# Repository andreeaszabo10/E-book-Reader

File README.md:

Szabo Cristina-Andreea
# E-book Reader
The project (Openbook) is an E-book reader built around the ESP32-C6-WROOM-1-N8 microcontroller, which integrates Wi-Fi and Bluetooth Low Energy functionality. It is responsible for managing communication between the connected components, sensor data acquisition, and display handling. The E-book reader has a 7.5-inch e-paper display, USB-C charging, a Li-Po battery, and 3 buttons.

## Block diagram:

## BOM - Bill of materials
| Component       | Device                | Link                                                                 | Datasheet                                                                 |
|-----------------|-----------------------|----------------------------------------------------------------------|---------------------------------------------------------------------------|
| BOOT_BUTTON     | BUTTON_CUSYOMV1        | [Link](https://ro.mouser.com/ProductDetail/Panasonic/EVQ-P7L01P?qs=rJ%252BziJWpyszWhhNszc02jQ%3D%3D&_gl=1*xzqk3l*_ga*dW5kZWZpbmVk*_ga_15W4STQT4T*dW5kZWZpbmVk*_ga_1KQLCYKRX3*dW5kZWZpbmVk)     | [Datasheet](https://componentsearchengine.com/Datasheets/2/EVQP7L01P.pdf) |
| C1              | ESP32_WROVER_EAGLE-LTSPICE_CC0402 | [Link](https://ro.mouser.com/ProductDetail/YAGEO/CC0402MRX5R5BB106?qs=zEY9bCHj09eCmUJdZuS5Lg%3D%3D)  | [Datasheet](https://componentsearchengine.com/Datasheets/2/CC0402MRX5R5BB106.pdf) |
| C1_BAT          | ESP32_WROVER_EAGLE-LTSPICE_CC0402 | [Link](https://ro.mouser.com/ProductDetail/YAGEO/CC0402MRX5R5BB106?qs=zEY9bCHj09eCmUJdZuS5Lg%3D%3D)  | [Datasheet](https://componentsearchengine.com/Datasheets/2/CC0402MRX5R5BB106.pdf) |
| C1_BAT1         | EAGLE-LTSPICE_CC0402   | [Link](https://ro.mouser.com/ProductDetail/YAGEO/CC0402MRX5R5BB106?qs=zEY9bCHj09eCmUJdZuS5Lg%3D%3D)  | [Datasheet](https://componentsearchengine.com/Datasheets/2/CC0402MRX5R5BB106.pdf) |
| C1_BAT2         | EAGLE-LTSPICE_CC0402   | [Link](https://ro.mouser.com/ProductDetail/YAGEO/CC0402MRX5R5BB106?qs=zEY9bCHj09eCmUJdZuS5Lg%3D%3D)  | [Datasheet](https://componentsearchengine.com/Datasheets/2/CC0402MRX5R5BB106.pdf) |
| C2              | ESP32_WROVER_EAGLE-LTSPICE_CC0402 | [Link](https://ro.mouser.com/ProductDetail/YAGEO/CC0402MRX5R5BB106?qs=zEY9bCHj09eCmUJdZuS5Lg%3D%3D)  | [Datasheet](https://componentsearchengine.com/Datasheets/2/CC0402MRX5R5BB106.pdf) |
| C2_BAT          | ESP32_WROVER_EAGLE-LTSPICE_CC0402 | [Link](https://ro.mouser.com/ProductDetail/YAGEO/CC0402MRX5R5BB106?qs=zEY9bCHj09eCmUJdZuS5Lg%3D%3D)  | [Datasheet](https://componentsearchengine.com/Datasheets/2/CC0402MRX5R5BB106.pdf) |
| C3              | RCL_CPOL-EUCT3528      | [Link](https://ro.mouser.com/ProductDetail/YAGEO/CC0402MRX5R5BB106?qs=zEY9bCHj09eCmUJdZuS5Lg%3D%3D)  | [Datasheet](https://componentsearchengine.com/Datasheets/2/CC0402MRX5R5BB106.pdf) |
| C4              | ESP32_WROVER_EAGLE-LTSPICE_CC0402 | [Link](https://ro.mouser.com/ProductDetail/YAGEO/CC0402MRX5R5BB106?qs=zEY9bCHj09eCmUJdZuS5Lg%3D%3D)  | [Datasheet](https://componentsearchengine.com/Datasheets/2/CC0402MRX5R5BB106.pdf) |
| C4_USB          | ESP32_WROVER_EAGLE-LTSPICE_CC0402 | [Link](https://ro.mouser.com/ProductDetail/YAGEO/CC0402MRX5R5BB106?qs=zEY9bCHj09eCmUJdZuS5Lg%3D%3D)  | [Datasheet](https://componentsearchengine.com/Datasheets/2/CC0402MRX5R5BB106.pdf) |
| C5              | ESP32_WROVER_EAGLE-LTSPICE_CC0402 | [Link](https://ro.mouser.com/ProductDetail/YAGEO/CC0402MRX5R5BB106?qs=zEY9bCHj09eCmUJdZuS5Lg%3D%3D)  | [Datasheet](https://componentsearchengine.com/Datasheets/2/CC0402MRX5R5BB106.pdf) |
| C5_USB          | ESP32_WROVER_EAGLE-LTSPICE_CC0402 | [Link](https://ro.mouser.com/ProductDetail/YAGEO/CC0402MRX5R5BB106?qs=zEY9bCHj09eCmUJdZuS5Lg%3D%3D)  | [Datasheet](https://componentsearchengine.com/Datasheets/2/CC0402MRX5R5BB106.pdf) |
| C6              | ESP32_WROVER_EAGLE-LTSPICE_CC0402 | [Link](https://ro.mouser.com/ProductDetail/YAGEO/CC0402MRX5R5BB106?qs=zEY9bCHj09eCmUJdZuS5Lg%3D%3D)  | [Datasheet](https://componentsearchengine.com/Datasheets/2/CC0402MRX5R5BB106.pdf) |
| C7              | ESP32_WROVER_EAGLE-LTSPICE_CC0402 | [Link](https://ro.mouser.com/ProductDetail/YAGEO/CC0402MRX5R5BB106?qs=zEY9bCHj09eCmUJdZuS5Lg%3D%3D)  | [Datasheet](https://componentsearchengine.com/Datasheets/2/CC0402MRX5R5BB106.pdf) |
| C8              | ESP32_WROVER_EAGLE-LTSPICE_CC0402 | [Link](https://ro.mouser.com/ProductDetail/YAGEO/CC0402MRX5R5BB106?qs=zEY9bCHj09eCmUJdZuS5Lg%3D%3D)  | [Datasheet](https://componentsearchengine.com/Datasheets/2/CC0402MRX5R5BB106.pdf) |
| C9              | EAGLE-LTSPICE_CC0402   | [Link](https://ro.mouser.com/ProductDetail/YAGEO/CC0402MRX5R5BB106?qs=zEY9bCHj09eCmUJdZuS5Lg%3D%3D)  | [Datasheet](https://componentsearchengine.com/Datasheets/2/CC0402MRX5R5BB106.pdf) |
| C10             | ESP32_WROVER_EAGLE-LTSPICE_CC0402 | [Link](https://ro.mouser.com/ProductDetail/YAGEO/CC0402MRX5R5BB106?qs=zEY9bCHj09eCmUJdZuS5Lg%3D%3D)  | [Datasheet](https://componentsearchengine.com/Datasheets/2/CC0402MRX5R5BB106.pdf) |
| C10_SUPERCAP    | CPH3225A               | [Link](https://ro.mouser.com/ProductDetail/Seiko-Semiconductors/CPH3225A?qs=3etwrb1wR%252BhUOph6lAO7eg%3D%3D) | [Datasheet](https://ro.mouser.com/datasheet/2/360/Seiko_Instruments_MicroBattery_E_20230330_2024Jan_-3561061.pdf) |
| CHANGE_BUTTON   | BUTTON_CUSYOMV1        | [Link](https://ro.mouser.com/ProductDetail/Panasonic/EVQ-P7L01P?qs=rJ%252BziJWpyszWhhNszc02jQ%3D%3D&_gl=1*xzqk3l*_ga*dW5kZWZpbmVk*_ga_15W4STQT4T*dW5kZWZpbmVk*_ga_1KQLCYKRX3*dW5kZWZpbmVk)     | [Datasheet](https://componentsearchengine.com/Datasheets/2/EVQP7L01P.pdf) |
| C_DELAY         | ESP32_WROVER_EAGLE-LTSPICE_CC0402 | [Link](https://ro.mouser.com/ProductDetail/YAGEO/CC0402MRX5R5BB106?qs=zEY9bCHj09eCmUJdZuS5Lg%3D%3D)  | [Datasheet](https://componentsearchengine.com/Datasheets/2/CC0402MRX5R5BB106.pdf) |
| D1              | USBLC6-2SC6Y           | [Link](https://ro.mouser.com/ProductDetail/STMicroelectronics/USBLC6-2SC6Y?qs=gNDSiZmRJS%2FOgDexvXkdow%3D%3D) | [Datasheet](https://ro.mouser.com/datasheet/2/389/usblc6_2sc6y-1852505.pdf) |
| D2              | ESP32_WROVER_AVX...SD0805S020S1R0_AVX_... | [Link](https://eu.mouser.com/ProductDetail/KYOCERA-AVX/SD0805S020S1R0?qs=jCA%252BPfw4LHbpkAoSnwrdjw%3D%3D) | [Datasheet](http://datasheets.avx.com/schottky.pdf) |
| D3              | MBR0530               | [Link](https://www.snapeda.com/parts/MBR0530/Onsemi/view-part/?ref=eda) | [Datasheet](https://www.snapeda.com/parts/MBR0530/Onsemi/view-part/?ref=eda) |
| D4              | MBR0530               | [Link](https://www.snapeda.com/parts/MBR0530/Onsemi/view-part/?ref=eda) | [Datasheet](https://www.snapeda.com/parts/MBR0530/Onsemi/view-part/?ref=eda) |
| D5              | MBR0530               | [Link](https://www.snapeda.com/parts/MBR0530/Onsemi/view-part/?ref=eda) | [Datasheet](https://www.snapeda.com/parts/MBR0530/Onsemi/view-part/?ref=eda) |
| D6              | PGB1010603MR          | [Link](https://www.snapeda.com/parts/PGB1010603MR/Littelfuse/view-part/?ref=eda) | [Datasheet](https://www.snapeda.com/parts/PGB1010603MR/Littelfuse/view-part/?ref=eda) |
| D7              | ESP32_WROVER_AVX---SD0805S020S1R0_AVX_... | [Link](https://eu.mouser.com/ProductDetail/KYOCERA-AVX/SD0805S020S1R0?qs=jCA%252BPfw4LHbpkAoSnwrdjw%3D%3D) | [Datasheet](http://datasheets.avx.com/schottky.pdf) |
| D8              | PGB1010603MR          | [Link](https://www.snapeda.com/parts/PGB1010603MR/Littelfuse/view-part/?ref=eda) | [Datasheet](https://www.snapeda.com/parts/PGB1010603MR/Littelfuse/view-part/?ref=eda) |
| D9              | PGB1010603MR          | [Link](https://www.snapeda.com/parts/PGB1010603MR/Littelfuse/view-part/?ref=eda) | [Datasheet](https://www.snapeda.com/parts/PGB1010603MR/Littelfuse/view-part/?ref=eda) |
| D10             | PGB1010603MR          | [Link](https://www.snapeda.com/parts/PGB1010603MR/Littelfuse/view-part/?ref=eda) | [Datasheet](https://www.snapeda.com/parts/PGB1010603MR/Littelfuse/view-part/?ref=eda) |
| D11             | PGB1010603MR          | [Link](https://www.snapeda.com/parts/PGB1010603MR/Littelfuse/view-part/?ref=eda) | [Datasheet](https://www.snapeda.com/parts/PGB1010603MR/Littelfuse/view-part/?ref=eda) |
| D12             | PGB1010603MR          | [Link](https://www.snapeda.com/parts/PGB1010603MR/Littelfuse/view-part/?ref=eda) | [Datasheet](https://www.snapeda.com/parts/PGB1010603MR/Littelfuse/view-part/?ref=eda) |
| EPD_C1          | ESP32_WROVER_EAGLE-LTSPICE_CC0402 | [Link](https://ro.mouser.com/ProductDetail/YAGEO/CC0402MRX5R5BB106?qs=zEY9bCHj09eCmUJdZuS5Lg%3D%3D)  | [Datasheet](https://componentsearchengine.com/Datasheets/2/CC0402MRX5R5BB106.pdf) |
| EPD_C2          | ESP32_WROVER_EAGLE-LTSPICE_CC0402 | [Link](https://ro.mouser.com/ProductDetail/YAGEO/CC0402MRX5R5BB106?qs=zEY9bCHj09eCmUJdZuS5Lg%3D%3D)  | [Datasheet](https://componentsearchengine.com/Datasheets/2/CC0402MRX5R5BB106.pdf) |
| EPD_C5          | ESP32_WROVER_EAGLE-LTSPICE_CC0402 | [Link](https://ro.mouser.com/ProductDetail/YAGEO/CC0402MRX5R5BB106?qs=zEY9bCHj09eCmUJdZuS5Lg%3D%3D)  | [Datasheet](https://componentsearchengine.com/Datasheets/2/CC0402MRX5R5BB106.pdf) |
| EPD_C6          | ESP32_WROVER_EAGLE-LTSPICE_CC0402 | [Link](https://ro.mouser.com/ProductDetail/YAGEO/CC0402MRX5R5BB106?qs=zEY9bCHj09eCmUJdZuS5Lg%3D%3D)  | [Datasheet](https://componentsearchengine.com/Datasheets/2/CC0402MRX5R5BB106.pdf) |
| EPD_C7          | ESP32_WROVER_EAGLE-LTSPICE_CC0402 | [Link](https://ro.mouser.com/ProductDetail/YAGEO/CC0402MRX5R5BB106?qs=zEY9bCHj09eCmUJdZuS5Lg%3D%3D)  | [Datasheet](https://componentsearchengine.com/Datasheets/2/CC0402MRX5R5BB106.pdf) |
| EPD_C8          | ESP32_WROVER_EAGLE-LTSPICE_CC0402 | [Link](https://ro.mouser.com/ProductDetail/YAGEO/CC0402MRX5R5BB106?qs=zEY9bCHj09eCmUJdZuS5Lg%3D%3D)  | [Datasheet](https://componentsearchengine.com/Datasheets/2/CC0402MRX5R5BB106.pdf) |
| EPD_C9          | ESP32_WROVER_EAGLE-LTSPICE_CC0402 | [Link](https://ro.mouser.com/ProductDetail/YAGEO/CC0402MRX5R5BB106?qs=zEY9bCHj09eCmUJdZuS5Lg%3D%3D)  | [Datasheet](https://componentsearchengine.com/Datasheets/2/CC0402MRX5R5BB106.pdf) |
| EPD_C10         | ESP32_WROVER_EAGLE-LTSPICE_CC0402 | [Link](https://ro.mouser.com/ProductDetail/YAGEO/CC0402MRX5R5BB106?qs=zEY9bCHj09eCmUJdZuS5Lg%3D%3D)  | [Datasheet](https://componentsearchengine.com/Datasheets/2/CC0402MRX5R5BB106.pdf) |
| EPD_C11         | ESP32_WROVER_EAGLE-LTSPICE_CC0402 | [Link](https://ro.mouser.com/ProductDetail/YAGEO/CC0402MRX5R5BB106?qs=zEY9bCHj09eCmUJdZuS5Lg%3D%3D)  | [Datasheet](https://componentsearchengine.com/Datasheets/2/CC0402MRX5R5BB106.pdf) |
| EPD_C12         | ESP32_WROVER_EAGLE-LTSPICE_CC0402 | [Link](https://ro.mouser.com/ProductDetail/YAGEO/CC0402MRX5R5BB106?qs=zEY9bCHj09eCmUJdZuS5Lg%3D%3D)  | [Datasheet](https://componentsearchengine.com/Datasheets/2/CC0402MRX5R5BB106.pdf) |
| IC1             | BD5229G-TR            | [Link](https://ro.mouser.com/ProductDetail/ROHM-Semiconductor/BD5229G-TR?qs=4kLU8WoGk0vvnhrrYwdszw%3D%3D) | [Datasheet](https://fscdn.rohm.com/en/products/databook/datasheet/ic/power/voltage_detector/bd52xxg-e.pdf) |
| IC4             | XC6220A331MR-G        | [Link](https://ro.mouser.com/ProductDetail/Torex-Semiconductor/XC6220A331MR-G?qs=AsjdqWjXhJ8ZSWznL1J0gg%3D%3D) | [Datasheet](https://ro.mouser.com/datasheet/2/760/xc6220-3371556.pdf) |
| J1              | FH34SRJ-24S-0.5SH_99_ | [Link](https://ro.mouser.com/ProductDetail/Hirose-Connector/FH34SRJ-24S-0.5SH99?qs=vcbW%252B4%252BSTIpKBl5ap9J8Fw%3D%3D) | [Datasheet](https://ro.mouser.com/datasheet/2/185/FH34SRJ_24S_0_5SH_99__CL0580_1255_6_99_2DDrawing_0-1615044.pdf) |
| J2              | USB4110-GF-A          | [Link](https://ro.mouser.com/ProductDetail/GCT/USB4110-GF-A?qs=KUoIvG%2F9IlYiZvIXQjyJeA%3D%3D) | [Datasheet](https://ro.mouser.com/datasheet/2/837/GCT_USB4110_Product_Drawing___20k_cycles-3455479.pdf) |
| J3              | QWIIC_CONNECTORJS-1MM | [Link](https://ro.mouser.com/ProductDetail/SparkFun/PRT-14417?qs=wd5RIQLrsJhgdz%2FpmZ%2F3GQ%3D%3D) | [Datasheet](https://ro.mouser.com/datasheet/2/813/Qwiic_Connector_Datasheet-1223982.pdf) |
| J4              | 112A-TAAR-R03_ATTEND  | [Link](https://store.comet.srl.ro/Catalogue/Product/43497/) | [Datasheet](https://store.comet.srl.ro/Catalogue/Product/43497/) |
| L1              | 744043680IND_4828-WE-TPC_WRE | [Link](https://ro.mouser.com/ProductDetail/Wurth-Elektronik/744043680?qs=PGXP4M47uW6VkZq%252BkzjrHA%3D%3D) | [Datasheet](https://eu.mouser.com/ProductDetail/Wurth-Elektronik/744043680?qs=PGXP4M47uW6VkZq%252BkzjrHA%3D%3D) |
| PFMF.050.1      | ESP32C6_VARISTORCN1812 | [Link](https://ro.mouser.com/ProductDetail/KEMET/VE1812K401R050?qs=OycAS1CGnlizCtaoDVbQTA%3D%3D) | [Datasheet](https://www.mouser.co.uk/ProductDetail/EPCOS-TDK/B72520T0350K062?qs=dEfas%2FXlABIszF52uu7vrg%3D%3D) |
| Q1              | DMG2305UX-7           | [Link](https://ro.mouser.com/ProductDetail/Diodes-Incorporated/DMG2305UX-7?qs=L1DZKBg7t5F%2FNBHrjfxC%252Bg%3D%3D) | [Datasheet](https://www.diodes.com/assets/Datasheets/DMG2305UX.pdf) |
| Q2              | ESP32_WROVER_SPARKFUN-DISCRETESEMI_MOSFET_... | [Link](https://ro.mouser.com/ProductDetail/Diodes-Incorporated/DMG2305UX-7?qs=L1DZKBg7t5F%2FNBHrjfxC%252Bg%3D%3D) | [Datasheet](https://www.diodes.com/assets/Datasheets/DMG2305UX.pdf) |
| Q3              | D8                    | [Link](https://ro.mouser.com/ProductDetail/Vishay-Semiconductors/SI1308EDL-T1-GE3?qs=bX1%252BNvsK%2FBramh9tgpOaEw%3D%3D) | [Datasheet](https://componentsearchengine.com/part-view/SI1308EDL-T1-GE3/Vishay) |
| R1              | ESP32_WROVER_EAGLE-LTSPICE_RR0402 | [Link](https://ro.mouser.com/ProductDetail/YAGEO/RC0402FR-07100KL?qs=mnq%2FyloZIXzTlUn7JAHSWg%3D%3D) | [Datasheet](https://ro.mouser.com/datasheet/2/447/YAGEO_PYu_RC_Group_51_RoHS_L_12-3313492.pdf) |
| R1_PINH         | ESP32_WROVER_EAGLE-LTSPICE_RR0402 | [Link](https://ro.mouser.com/ProductDetail/YAGEO/RC0402FR-07100KL?qs=mnq%2FyloZIXzTlUn7JAHSWg%3D%3D) | [Datasheet](https://ro.mouser.com/datasheet/2/447/YAGEO_PYu_RC_Group_51_RoHS_L_12-3313492.pdf) |
| R1_PINH1        | ESP32_WROVER_EAGLE-LTSPICE_RR0402 | [Link](https://ro.mouser.com/ProductDetail/YAGEO/RC0402FR-07100KL?qs=mnq%2FyloZIXzTlUn7JAHSWg%3D%3D) | [Datasheet](https://ro.mouser.com/datasheet/2/447/YAGEO_PYu_RC_Group_51_RoHS_L_12-3313492.pdf) |
| R1_BAT          | ESP32_WROVER_EAGLE-LTSPICE_RR0402 | [Link](https://ro.mouser.com/ProductDetail/YAGEO/RC0402FR-07100KL?qs=mnq%2FyloZIXzTlUn7JAHSWg%3D%3D) | [Datasheet](https://ro.mouser.com/datasheet/2/447/YAGEO_PYu_RC_Group_51_RoHS_L_12-3313492.pdf) |
| R1_PWRUSB       | ESP32_WROVER_EAGLE-LTSPICE_RR0402 | [Link](https://ro.mouser.com/ProductDetail/YAGEO/RC0402FR-07100KL?qs=mnq%2FyloZIXzTlUn7JAHSWg%3D%3D) | [Datasheet](https://ro.mouser.com/datasheet/2/447/YAGEO_PYu_RC_Group_51_RoHS_L_12-3313492.pdf) |
| R2              | ESP32_WROVER_EAGLE-LTSPICE_RR0402 | [Link](https://ro.mouser.com/ProductDetail/YAGEO/RC0402FR-07100KL?qs=mnq%2FyloZIXzTlUn7JAHSWg%3D%3D) | [Datasheet](https://ro.mouser.com/datasheet/2/447/YAGEO_PYu_RC_Group_51_RoHS_L_12-3313492.pdf) |
| R2_PINH         | ESP32_WROVER_EAGLE-LTSPICE_RR0402 | [Link](https://ro.mouser.com/ProductDetail/YAGEO/RC0402FR-07100KL?qs=mnq%2FyloZIXzTlUn7JAHSWg%3D%3D) | [Datasheet](https://ro.mouser.com/datasheet/2/447/YAGEO_PYu_RC_Group_51_RoHS_L_12-3313492.pdf) |
| R2_PINH1        | ESP32_WROVER_EAGLE-LTSPICE_RR0402 | [Link](https://ro.mouser.com/ProductDetail/YAGEO/RC0402FR-07100KL?qs=mnq%2FyloZIXzTlUn7JAHSWg%3D%3D) | [Datasheet](https://ro.mouser.com/datasheet/2/447/YAGEO_PYu_RC_Group_51_RoHS_L_12-3313492.pdf) |
| R2_USB          | ESP32_WROVER_EAGLE-LTSPICE_RR0402 | [Link](https://ro.mouser.com/ProductDetail/YAGEO/RC0402FR-07100KL?qs=mnq%2FyloZIXzTlUn7JAHSWg%3D%3D) | [Datasheet](https://ro.mouser.com/datasheet/2/447/YAGEO_PYu_RC_Group_51_RoHS_L_12-3313492.pdf) |
| R2_USB1         | ESP32_WROVER_EAGLE-LTSPICE_RR0402 | [Link](https://ro.mouser.com/ProductDetail/YAGEO/RC0402FR-07100KL?qs=mnq%2FyloZIXzTlUn7JAHSWg%3D%3D) | [Datasheet](https://ro.mouser.com/datasheet/2/447/YAGEO_PYu_RC_Group_51_RoHS_L_12-3313492.pdf) |
| R2_BAT          | ESP32_WROVER_EAGLE-LTSPICE_RR0402 | [Link](https://ro.mouser.com/ProductDetail/YAGEO/RC0402FR-07100KL?qs=mnq%2FyloZIXzTlUn7JAHSWg%3D%3D) | [Datasheet](https://ro.mouser.com/datasheet/2/447/YAGEO_PYu_RC_Group_51_RoHS_L_12-3313492.pdf) |
| R3              | ESP32_WROVER_EAGLE-LTSPICE_RR0402 | [Link](https://ro.mouser.com/ProductDetail/YAGEO/RC0402FR-07100KL?qs=mnq%2FyloZIXzTlUn7JAHSWg%3D%3D) | [Datasheet](https://ro.mouser.com/datasheet/2/447/YAGEO_PYu_RC_Group_51_RoHS_L_12-3313492.pdf) |
| R4              | ESP32_WROVER_EAGLE-LTSPICE_RR0402 | [Link](https://ro.mouser.com/ProductDetail/YAGEO/RC0402FR-07100KL?qs=mnq%2FyloZIXzTlUn7JAHSWg%3D%3D) | [Datasheet](https://ro.mouser.com/datasheet/2/447/YAGEO_PYu_RC_Group_51_RoHS_L_12-3313492.pdf) |
| R5              | ESP32_WROVER_EAGLE-LTSPICE_RR0402 | [Link](https://ro.mouser.com/ProductDetail/YAGEO/RC0402FR-07100KL?qs=mnq%2FyloZIXzTlUn7JAHSWg%3D%3D) | [Datasheet](https://ro.mouser.com/datasheet/2/447/YAGEO_PYu_RC_Group_51_RoHS_L_12-3313492.pdf) |
| R6              | ESP32_WROVER_EAGLE-LTSPICE_RR0402 | [Link](https://ro.mouser.com/ProductDetail/YAGEO/RC0402FR-07100KL?qs=mnq%2FyloZIXzTlUn7JAHSWg%3D%3D) | [Datasheet](https://ro.mouser.com/datasheet/2/447/YAGEO_PYu_RC_Group_51_RoHS_L_12-3313492.pdf) |
| R7              | ESP32_WROVER_EAGLE-LTSPICE_RR0402 | [Link](https://ro.mouser.com/ProductDetail/YAGEO/RC0402FR-07100KL?qs=mnq%2FyloZIXzTlUn7JAHSWg%3D%3D) | [Datasheet](https://ro.mouser.com/datasheet/2/447/YAGEO_PYu_RC_Group_51_RoHS_L_12-3313492.pdf) |
| R8              | ESP32_WROVER_EAGLE-LTSPICE_RR0402 | [Link](https://ro.mouser.com/ProductDetail/YAGEO/RC0402FR-07100KL?qs=mnq%2FyloZIXzTlUn7JAHSWg%3D%3D) | [Datasheet](https://ro.mouser.com/datasheet/2/447/YAGEO_PYu_RC_Group_51_RoHS_L_12-3313492.pdf) |
| R9              | ESP32_WROVER_EAGLE-LTSPICE_RR0402 | [Link](https://ro.mouser.com/ProductDetail/YAGEO/RC0402FR-07100KL?qs=mnq%2FyloZIXzTlUn7JAHSWg%3D%3D) | [Datasheet](https://ro.mouser.com/datasheet/2/447/YAGEO_PYu_RC_Group_51_RoHS_L_12-3313492.pdf) |
| R10             | ESP32_WROVER_EAGLE-LTSPICE_RR0402 | [Link](https://ro.mouser.com/ProductDetail/YAGEO/RC0402FR-07100KL?qs=mnq%2FyloZIXzTlUn7JAHSWg%3D%3D) | [Datasheet](https://ro.mouser.com/datasheet/2/447/YAGEO_PYu_RC_Group_51_RoHS_L_12-3313492.pdf) |
| RESET_BUTTON    | BUTTON_CUSYOMV1        | [Link](https://ro.mouser.com/ProductDetail/Panasonic/EVQ-P7L01P?qs=rJ%252BziJWpyszWhhNszc02jQ%3D%3D&_gl=1*xzqk3l*_ga*dW5kZWZpbmVk*_ga_15W4STQT4T*dW5kZWZpbmVk*_ga_1KQLCYKRX3*dW5kZWZpbmVk)     | [Datasheet](https://componentsearchengine.com/Datasheets/2/EVQP7L01P.pdf) |
| R_BOOT          | ESP32_WROVER_EAGLE-LTSPICE_RR0402 | [Link](https://ro.mouser.com/ProductDetail/YAGEO/RC0402FR-07100KL?qs=mnq%2FyloZIXzTlUn7JAHSWg%3D%3D) | [Datasheet](https://ro.mouser.com/datasheet/2/447/YAGEO_PYu_RC_Group_51_RoHS_L_12-3313492.pdf) |
| R_CAPACITOR     | ESP32_WROVER_EAGLE-LTSPICE_RR0402 | [Link](https://ro.mouser.com/ProductDetail/YAGEO/RC0402FR-07100KL?qs=mnq%2FyloZIXzTlUn7JAHSWg%3D%3D) | [Datasheet](https://ro.mouser.com/datasheet/2/447/YAGEO_PYu_RC_Group_51_RoHS_L_12-3313492.pdf) |
| R_CHANGE        | ESP32_WROVER_EAGLE-LTSPICE_RR0402 | [Link](https://ro.mouser.com/ProductDetail/YAGEO/RC0402FR-07100KL?qs=mnq%2FyloZIXzTlUn7JAHSWg%3D%3D) | [Datasheet](https://ro.mouser.com/datasheet/2/447/YAGEO_PYu_RC_Group_51_RoHS_L_12-3313492.pdf) |
| R_CL1           | ESP32_WROVER_EAGLE-LTSPICE_RR0402 | [Link](https://ro.mouser.com/ProductDetail/YAGEO/RC0402FR-07100KL?qs=mnq%2FyloZIXzTlUn7JAHSWg%3D%3D) | [Datasheet](https://ro.mouser.com/datasheet/2/447/YAGEO_PYu_RC_Group_51_RoHS_L_12-3313492.pdf) |
| R_RESET         | ESP32_WROVER_EAGLE-LTSPICE_RR0402 | [Link](https://ro.mouser.com/ProductDetail/YAGEO/RC0402FR-07100KL?qs=mnq%2FyloZIXzTlUn7JAHSWg%3D%3D) | [Datasheet](https://ro.mouser.com/datasheet/2/447/YAGEO_PYu_RC_Group_51_RoHS_L_12-3313492.pdf) |
| SENSOR2         | ESP32_WROVER_BME680_BME680 | [Link](https://ro.mouser.com/ProductDetail/Bosch-Sensortec/BME680?qs=v271MhAjFHjo0yA%2FC4OnDQ%3D%3D) | [Datasheet](https://ro.mouser.com/datasheet/2/783/BST_BME680_DS001-1509608.pdf) |
| SJ1             | SJ                     | [Link](https://grabcad.com/library/solder-jumpers-1)                | [Datasheet](https://grabcad.com/library/solder-jumpers-1)                |
| TP1 - TP17      | TPTP20R               | -                                                               | -                                                                    |
| U1              | W25Q512JVEIQ          | [Link](https://ro.mouser.com/ProductDetail/Winbond/W25Q512JVEIQ?qs=l7cgNqFNU1jw6svr3at6tA%3D%3D)     | [Datasheet](https://ro.mouser.com/datasheet/2/949/Winbond_W25Q512JV_Datasheet-3240039.pdf) |
| U2              | ESP32-C6-WROOM-1-N8   | [Link](https://ro.mouser.com/ProductDetail/Espressif-Systems/ESP32-C6-WROOM-1-N8?qs=8Wlm6%252BaMh8ST02Gmwp74cw%3D%3D) | [Datasheet](https://ro.mouser.com/datasheet/2/891/Espressif_ESP32_C6_WROOM_1__Datasheet_V0_1_PRELIMI-3239987.pdf) |
| U3              | DS3231SN#             | [Link](https://ro.mouser.com/ProductDetail/Analog-Devices-Maxim-Integrated/DS3231SN?qs=1eQvB6Dk1vhUlr8%2FOrV0Fw%3D%3D) | [Datasheet](https://ro.mouser.com/datasheet/2/609/DS3231-3421123.pdf) |
| U4              | MAX17048G+T10         | [Link](https://ro.mouser.com/ProductDetail/Analog-Devices-Maxim-Integrated/MAX17048G%2bT10?qs=D7PJwyCwLAoGnnn8jEPRBQ%3D%3D) | [Datasheet](https://ro.mouser.com/datasheet/2/609/MAX17048_MAX17049-3469099.pdf) |
| U5              | ESP32_WROVER_SPARKFUN-IC-POWER_MCP73831 | [Link](https://ro.mouser.com/ProductDetail/Microchip-Technology/MCP73831T-2ACI-OT?qs=yUQqVecv4qvbBQBGbHx0Mw%3D%3D) | [Datasheet](https://ro.mouser.com/datasheet/2/268/MCP73831_Family_Data_Sheet_DS20001984H-3441711.pdf) |

## Hardware description:
- ESP32-C6-WROOM-1-N8: The most important part of the system, providing Wi-Fi and BLE capabilities for wireless communication.
- BME688: An environmental and air quality sensor that measures temperature, humidity, pressure, and gas. It communicates with the ESP32 via the I2C protocol.
- DS3231SN: A high-precision Real-Time Clock (RTC) module, connected via I2C.
- MAX17048: A battery level monitor with I2C interface, used to provide the State of Charge (SOC) estimation for the battery.
- SD Card Module: Provides local data storage, communicating with the ESP32 using the SPI protocol for faster read/write operations.
- E-Ink Display: A low-power e-paper display with an SPI interface for minimal energy consumption. It includes the following control signals: EPD_CS, EPD_DC, EPD_RST, and EPD_BUSY.
- W25Q512JVEIQ (64MB NOR Flash): External flash memory connected via SPI, used for storing firmware or large datasets.
- BOOT and RESET Buttons: Connected to GPIO pins to manage the bootloader activation and system reset.
- MCP73831: A Li-Po battery charging controller, responsible for managing the charging process of the battery.
- XC6220A331MR-G (LDO Regulator): A 3.3V voltage regulator that powers the logic circuits of the system from the battery or USB input.
- USB-C Port (USB4110-GF-A): Provides power input and serves as the serial interface for code uploading and debugging.

## Pins description:
- IO0 - INT_RTC: Interrupt signal from the RTC that can wake up the ESP32 from deep sleep. This pin is used by the RTC.
- IO1 – 32KHZ: The 32.768 kHz clock output from the DS3231 RTC, routed to the ESP32 for accurate timekeeping.
- IO2 – MISO: This is the Master In Slave Out pin for SPI communication, used for NOR Flash, E-Paper, and microSD data transfer.
- IO3 - EPD_BUSY: E-Ink Display status signal that indicates whether the screen is busy. The ESP32 reads this to determine when it can send the next display update.
- IO4 – SS_SD: SPI Select pin for the microSD card, ensuring it does not conflict with other SPI devices using Chip Select (CS) lines.
- IO5 – EPD_DC: E-Ink Display Data/Command line used to differentiate between command and data states.
- IO6 – SCK: The SPI Clock pin, used to synchronize data transmission for peripherals like NOR Flash, E-Paper, and microSD.
- IO7 – MOSI: Master Out Slave In pin for SPI communication, used to send data to NOR Flash, E-Paper, and microSD.
- IO9 – IO/BOOT: This is a GPIO pin used for entering programming mode and activating the bootloader when the system is powered on.
- IO10 - EPD_CS: E-Ink Display Chip Select pin, allowing the display to be selected during SPI communication without interfering with other devices.
- IO11 – FLASH_CS: Chip Select pin for the NOR Flash memory, used to activate the flash memory module during SPI communication.
- IO12 – USB_D-: USB Data- line, directly connected to the USB-C connector, enabling power input and data transfer for code uploading and debugging.
- IO13 – USB_D+: USB Data+ line, also routed to the USB-C connector, enabling data transfer for serial communication and debugging.
- IO15 – IO/CHANGE: A GPIO pin used for user-defined actions, such as navigating between pages or changing modes.
- IO16 – TX: Serial Transmit pin used for flashing the older ESP chips and for serial debug logs.
- IO17 – RX: Serial Receive pin used for receiving data during flashing and for serial communication in debug mode.
- IO18 – RTC_RST: Manual Reset pin for the RTC module. It can be used to reset the RTC for synchronization or during a watchdog reset.
- IO19 – I2C_PW: Provides 3.3V to power I2C peripherals, including the RTC, BME688, and battery gauge modules.
- IO20 – EPD_3V3_C: A 3.3V supply line dedicated to powering the E-Ink Display.
- IO21 – SDA: I2C Data line used for communication with the RTC, BME688, and other I2C devices.
- IO22 – SCL: I2C Clock line used for synchronization of data transfer between the ESP32 and I2C devices.
- IO23 – EPD_RST: E-Ink Display Reset pin used to initialize the display before any updates or during power-up.

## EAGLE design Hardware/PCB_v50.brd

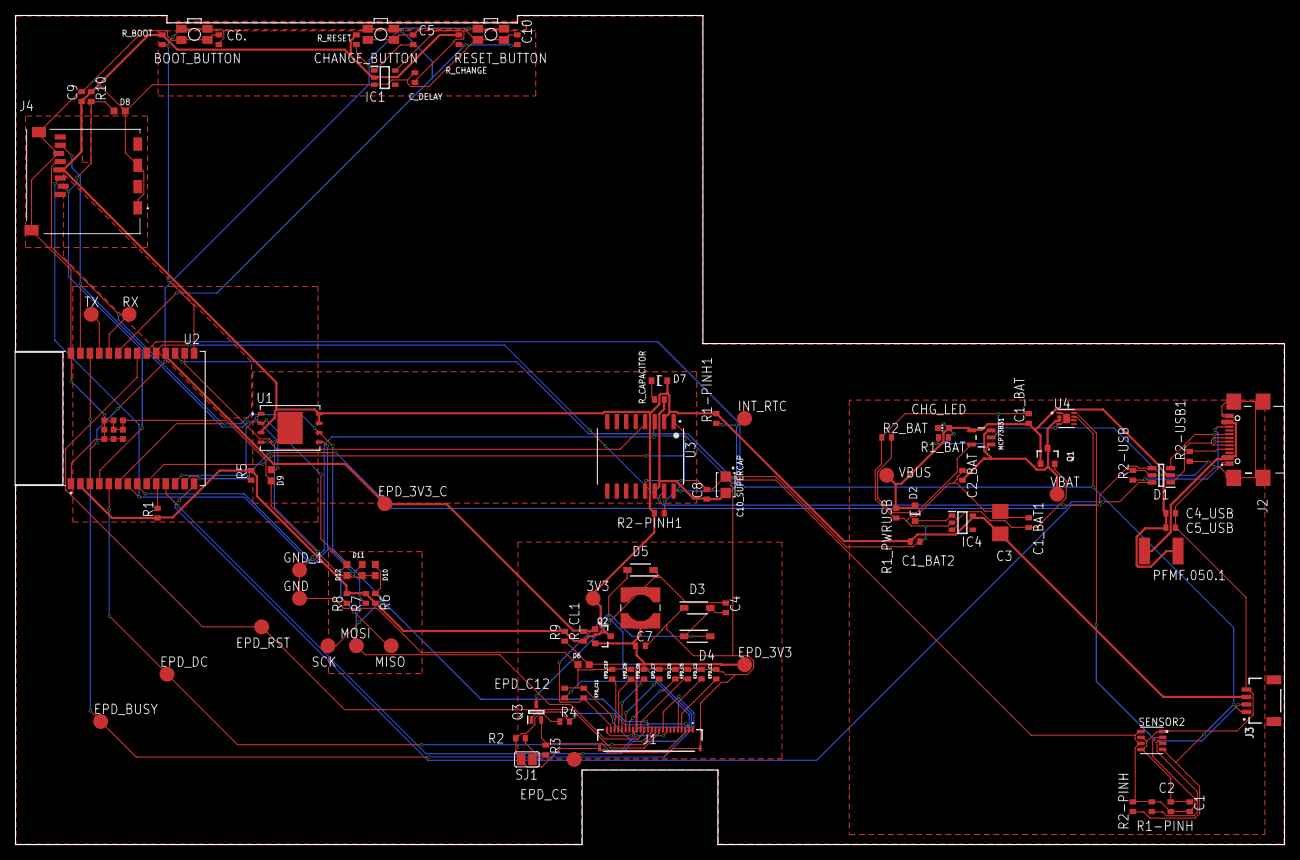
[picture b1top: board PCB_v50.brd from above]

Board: 2 copper layers, 170.2 x 111.2 mm, 103 parts (0 on the bottom side), 56 nets.

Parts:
3V3: TPTP20R; TP20R
BOOT_BUTTON: BUTTON_CUSYOMV1; MYBUTTON
C1, C2, C4_USB, C6., C8, C9, C10: 100nF; ESP32_WROVER_EAGLE-LTSPICE_C0402
C1_BAT, C1_BAT2, C2_BAT: 4.7nF; ESP32_WROVER_EAGLE-LTSPICE_C0402
C1_BAT1, C5_USB: 4.7uF; ESP32_WROVER_EAGLE-LTSPICE_C0402
C3: 100nF; RCL_CT3528
C4: 4.7uF/25V; ESP32_WROVER_EAGLE-LTSPICE_C0402
C5: 1uF; ESP32_WROVER_EAGLE-LTSPICE_C0402
C7: 10uF; ESP32_WROVER_EAGLE-LTSPICE_C0402
C10_SUPERCAP: CPH3225A; CAPCP3225X100N
CHANGE_BUTTON: BUTTON_CUSYOMV1; MYBUTTON
CHG_LED: 0; ADAFRUIT_CHIP-LED0603
C_DELAY: 100nF; ESP32_WROVER_EAGLE-LTSPICE_C0402
D1: USBLC6-2SC6Y; SOT95P280X145-6N
D2: ESP32_WROVER_AVX---SD0805S020S1R0_AVX_SD0805S020S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; ESP32_WROVER_AVX---SD0805S020S1R0_AVX_SD0805S020S1R0_0
D3, D4, D5: MBR0530; SOD3716X135N
D6, D8, D9, D10, D11, D12: PGB1010603MR; DIOC1608X36N
D7: SD0805S020S1R0; ESP32_WROVER_AVX---SD0805S020S1R0_AVX_SD0805S020S1R0_0
EPD_3V3, EPD_3V3_C: TPTP20R; TP20R
EPD_BUSY: TPTP20R; TP20R
EPD_C1, EPD_C2, EPD_C6, EPD_C7, EPD_C8, EPD_C9, EPD_C10, EPD_C11, EPD_C12: 1uF/50V; ESP32_WROVER_EAGLE-LTSPICE_C0402
EPD_C5: 0.1uF/50V; ESP32_WROVER_EAGLE-LTSPICE_C0402
EPD_CS: TPTP20R; TP20R
EPD_DC: TPTP20R; TP20R
EPD_RST: TPTP20R; TP20R
GND: TPTP20R; TP20R
GND_1: TPTP20R; TP20R
IC1: BD5229G-TR; SOT95P280X125-5N
IC4: XC6220A331MR-G; SOT95P280X120-5N
INT_RTC: TPTP20R; TP20R
J1: FH34SRJ-24S-0.5SH_99_; FH34SRJ24S05SH99
J2: SAMACSYS_PARTS_USB4110-GF-A; SAMACSYS_PARTS_USB4110GFA
J3: QWIIC_RIGHT_ANGLE; JST04_1MM_RA
J4: 112A-TAAR-R03_ATTEND; 112ATAARR03ATTEND
L1: 68uH; IND_4828-WE-TPC_WRE
MCP73831: MCP73831; ESP32_WROVER_SPARKFUN-IC-POWER_SOT23-5
MISO: TPTP20R; TP20R
MOSI: TPTP20R; TP20R
PFMF.050.1: ESP32C6_VARISTORCN1812; ESP32C6_VARISTOR_CT/CN1812
Q1, Q2: 20V/4.2A/52mΩ/1.4W; ESP32_WROVER_SPARKFUN-DISCRETESEMI_SOT23-3
Q3: SI1308EDL-T1-GE3; SOT65P210X110-3N
R1, R1-PINH, R1-PINH1, R2-PINH, R2-PINH1, R4, R5, R6, R7, R8, R9, R10: 10K; ESP32_WROVER_EAGLE-LTSPICE_R0402
R1_BAT: 200; ESP32_WROVER_EAGLE-LTSPICE_R0402
R1_PWRUSB: 100K; ESP32_WROVER_EAGLE-LTSPICE_R0402
R2: 2.2; ESP32_WROVER_EAGLE-LTSPICE_R0402
R2-USB, R2-USB1: 5K1; ESP32_WROVER_EAGLE-LTSPICE_R0402
R2_BAT: 2K; ESP32_WROVER_EAGLE-LTSPICE_R0402
R3: 0.47; ESP32_WROVER_EAGLE-LTSPICE_R0402
RESET_BUTTON: BUTTON_CUSYOMV1; MYBUTTON
RX: TPTP20R; TP20R
R_BOOT: 10K; ESP32_WROVER_EAGLE-LTSPICE_R0402
R_CAPACITOR: 15; ESP32_WROVER_EAGLE-LTSPICE_R0402
R_CHANGE: 10K; ESP32_WROVER_EAGLE-LTSPICE_R0402
R_CL1: 10K; ESP32_WROVER_EAGLE-LTSPICE_R0402
R_RESET: 10K; ESP32_WROVER_EAGLE-LTSPICE_R0402
SCK: TPTP20R; TP20R
SENSOR2: BME680; ESP32_WROVER_BME680_PSON80P300X300X100-8N
SJ1: 0; SJ
TX: TPTP20R; TP20R
U1: W25Q512JVEIQ; SON127P600X800X80-9N
U2: ESP32-C6-WROOM-1-N8; XCVR_ESP32-C6-WROOM-1-N8
U3: DS3231SN#; SOIC127P1032X265-16N
U4: MAX17048G+T10; SON50P200X200X80-9N
VBAT: TPTP20R; TP20R
VBUS: TPTP20R; TP20R

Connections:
3V3: 3V3.TP, C1_BAT2.1, C3.+, C9.1, D7.2, IC1.2, IC4.5, J3.3, J4.P4, Q2.3, R1.1, R1-PINH1.2, R2-PINH1.2, R5.2, R6.2, R7.2, R8.2, R9.2, R10.2, R_BOOT.2, R_CHANGE.2, R_CL1.1, R_RESET.2, U1.3, U1.7, U1.8, U2.2, U3.2
32KHZ: R2-PINH1.1, U2.9, U3.1
DN: D1.1, J2.A7, J2.B7
DP: D1.3, J2.A6, J2.B6
EPD_3V3: C7.1, EPD_3V3.TP, J1.16, L1.2, Q2.2
EPD_3V3_C: EPD_3V3_C.TP, Q2.1, R_CL1.2, U2.18
EPD_BUSY: EPD_BUSY.TP, J1.9, U2.26
EPD_CS: D6.2, EPD_CS.TP, J1.12, R9.1, U2.11
EPD_DC: EPD_DC.TP, J1.11, U2.5
EPD_RST: EPD_RST.TP, J1.10, U2.21
FLASH_CS: D9.2, R5.1, U1.1, U2.12
GDR: J1.2, Q3.1, R4.2
GND: BOOT_BUTTON.1, BOOT_BUTTON.2, C1.2, C1_BAT.2, C1_BAT1.2, C1_BAT2.2, C2.2, C2_BAT.2, C3.-, C4_USB.2, C5.2, C5_USB.2, C6..2, C7.2, C8.2, C9.2, C10.2, C10_SUPERCAP.1, CHANGE_BUTTON.1, CHANGE_BUTTON.2, C_DELAY.2, D1.5, D3.1, D6.1, D8.1, D9.1, D10.1, D11.1, D12.1, EPD_C1.2, EPD_C2.2, EPD_C5.2, EPD_C6.2, EPD_C7.2, EPD_C8.2, EPD_C9.2, EPD_C10.2, EPD_C11.2, EPD_C12.2, GND.TP, GND_1.TP, IC1.3, IC4.2, J1.8, J1.17, J1.MP1, J1.MP2, J2.A1, J2.A12, J2.B1, J2.B12, J2.MP1, J2.MP2, J2.MP3, J2.MP4, J3.4, J4.G1, J4.G2, J4.G3, J4.G4, J4.P6, MCP73831.2, R1_PWRUSB.1, R2.1, R2-USB.2, R2-USB1.1, R2_BAT.1, R4.1, RESET_BUTTON.1, RESET_BUTTON.2, SENSOR2.1, SENSOR2.5, SENSOR2.7, SJ1.1, U1.4, U1.9, U2.1, U2.28, U2.29_1, U2.29_2, U2.29_3, U2.29_4, U2.29_5, U2.29_6, U2.29_7, U2.29_8, U2.29_9, U3.13, U4.1, U4.4, U4.6, U4.9
GPIO8: R1.2, U2.10
I2C_PW: C1.1, C2.1, R1-PINH.2, R2-PINH.2, SENSOR2.2, SENSOR2.6, SENSOR2.8, U2.17
INT_RTC: INT_RTC.TP, R1-PINH1.1, U2.8, U3.3
IO/BOOT: BOOT_BUTTON.3, BOOT_BUTTON.4, C6..1, R_BOOT.1, U2.15
IO/CHANGE: C10.1, CHANGE_BUTTON.3, CHANGE_BUTTON.4, R_CHANGE.1, U2.23
MISO: D12.2, J4.P7, MISO.TP, R8.1, U1.2, U2.27
MOSI: D11.2, J1.14, J4.P3, MOSI.TP, R7.1, U1.5, U2.7
unnamed: J2.A5, R2-USB1.2
unnamed: J2.B5, R2-USB.1
unnamed: CHG_LED.C, R1_BAT.2
unnamed: C1_BAT1.1, D2.1, IC4.1, IC4.3, Q1.2
unnamed: MCP73831.5, R2_BAT.2
unnamed: MCP73831.1, R1_BAT.1
unnamed: EPD_C5.1, J1.15
unnamed: EPD_C1.1, J1.4
unnamed: EPD_C6.1, J1.18
unnamed: C4.1, D3.2, D4.1
unnamed: EPD_C12.1, J1.24
unnamed: C_DELAY.1, IC1.5
unnamed: EPD_C10.1, J1.22
unnamed: EPD_C8.1, J1.20
unnamed: EPD_C7.1, J1.19
unnamed: EPD_C2.1, J1.5
unnamed: D7.1, R_CAPACITOR.1
PREVGH: D5.2, EPD_C9.1, J1.21
PREVGL: D4.2, EPD_C11.1, J1.23
RESE: J1.3, Q3.2, R3.2
RESE': R2.2, R3.1, SJ1.2
RESET: C5.1, IC1.1, RESET_BUTTON.3, RESET_BUTTON.4, R_RESET.1, U2.3
RTC_RST: U2.16, U3.4
RX: RX.TP, U2.24
SCK: D10.2, J1.13, J4.P5, R6.1, SCK.TP, U1.6, U2.6
SCL: J3.1, R2-PINH.1, SENSOR2.4, U2.20, U3.16, U4.7
SDA: J3.2, R1-PINH.1, SENSOR2.3, U2.19, U3.15, U4.8
SRC: C4.2, D5.1, L1.1, Q3.3
SS_SD: D8.2, J4.P2, R10.1, U2.4
TX: TX.TP, U2.25
USB_D+: D1.4, U2.14
USB_D-: D1.6, U2.13
VBAT: C2_BAT.1, MCP73831.3, Q1.3, U4.2, U4.3, VBAT.TP
VBUS: C1_BAT.1, C4_USB.1, C5_USB.1, CHG_LED.A, D1.2, D2.2, MCP73831.4, PFMF.050.1.2, Q1.1, R1_PWRUSB.2, VBUS.TP
VRTC: C8.1, C10_SUPERCAP.2, R_CAPACITOR.2, U3.14
VUSB: J2.A4, J2.A9, J2.B4, J2.B9, PFMF.050.1.1

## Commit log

2025-04-06 added project
2025-04-06 Create LICENSE
2025-04-14 update images
2025-04-14 update hardware

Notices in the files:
parts and their libraries:
COPYRIGHT: Copyright (C) 2024 Ultra Librarian. All rights reserved.
